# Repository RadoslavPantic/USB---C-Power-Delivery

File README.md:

# 100W USB-C Power Delivery Module

A high-power USB-C Power Delivery (PD) module capable of delivering up to **100W (20V @ 5A)**. 

---

## Project Contents

This repository includes:
- KiCad design files (`.kicad_pro`, `.kicad_pcb`, `.kicad_sch`)
- **Gerber files** for PCB fabrication
- **BOM** file (`usb_c_pd_source.csv`)

---

## Description

The project is based around the STUSB4710 Autonomous USB PD controller IC. The design functions as a power source with short-circuit protection and Vbus monitoring.
The project is configured in a buck topology, meaning there is a constant 24 V DC voltage at the input of the circuit. Using the TPS56837HRPAR buck converter, the PD IC sets the output USB-C compliant voltage. The project is hardware-heavy — the MCU is only needed to monitor the buck converter and to increase the current on the 20 V PDO from 2.25 A to 5 A

## Schematic

The schematic of the circuit is shown below:

---

## 3D View

The 3D render of the assembled PCB:

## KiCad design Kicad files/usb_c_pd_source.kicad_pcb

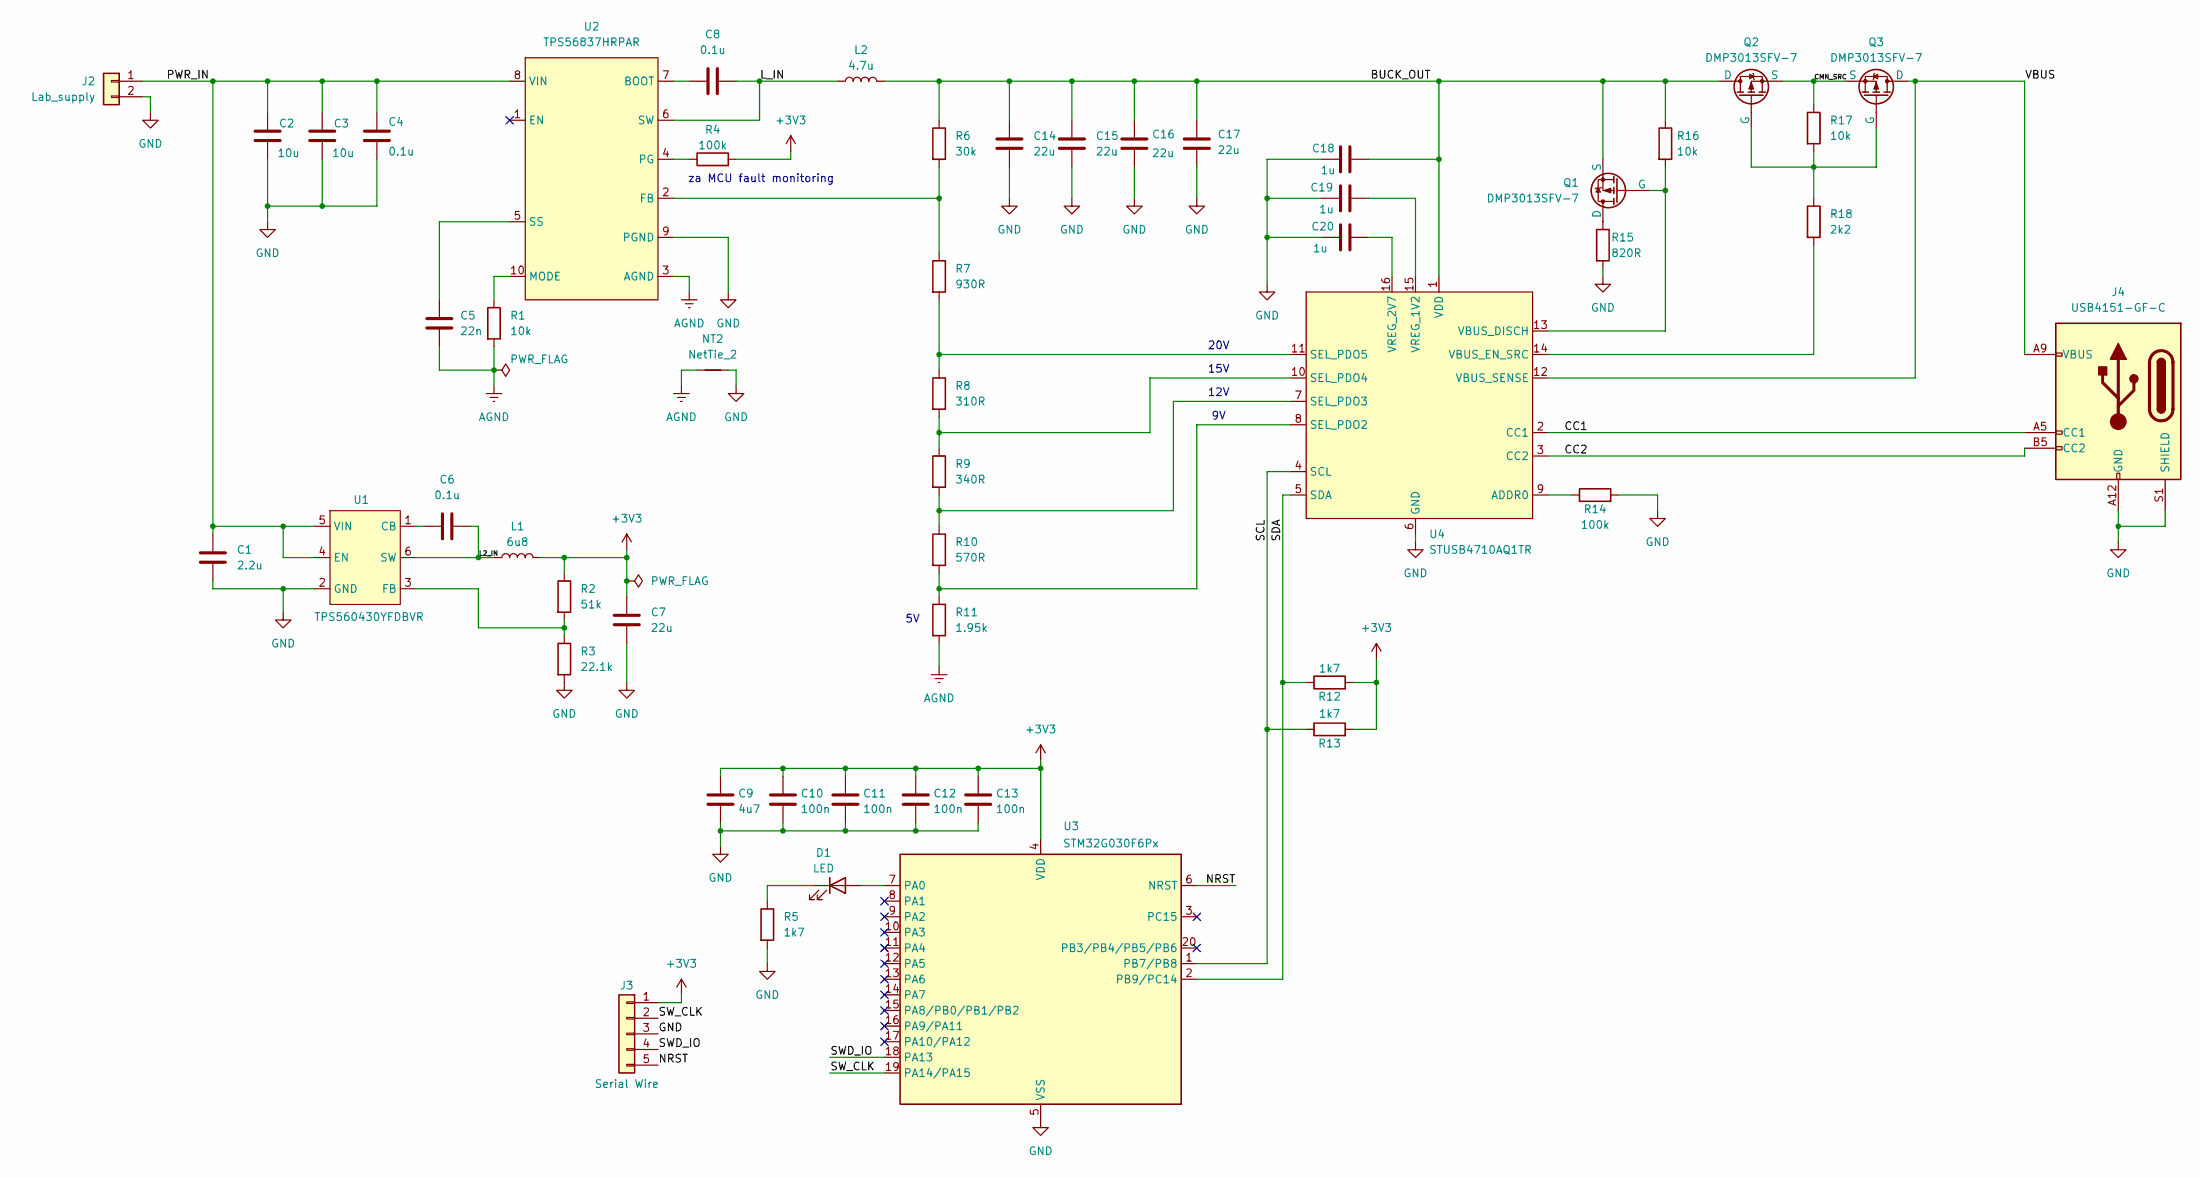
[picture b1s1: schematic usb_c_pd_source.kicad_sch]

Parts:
C1: 2.2u; C_0805_2012Metric_Pad1.18x1.45mm_HandSolder
C2, C3: 10u; C_0805_2012Metric_Pad1.18x1.45mm_HandSolder
C4, C6: 0.1u; C_0805_2012Metric_Pad1.18x1.45mm_HandSolder
C5: 22n; C_0603_1608Metric
C7, C14, C15, C16, C17: 22u; C_0805_2012Metric_Pad1.18x1.45mm_HandSolder
C8: 0.1u; C_0603_1608Metric
C9: 4u7; C_0805_2012Metric_Pad1.18x1.45mm_HandSolder
C10, C11, C12, C13: 100n; C_0805_2012Metric_Pad1.18x1.45mm_HandSolder
C18, C19, C20: 1u; C_0805_2012Metric_Pad1.18x1.45mm_HandSolder
D1: LED; LED_0805_2012Metric
J2: Lab_supply; PhoenixContact_MC_1,5_2-G-3.5_1x02_P3.50mm_Horizontal
J3: Serial Wire; PinHeader_1x05_P2.54mm_Vertical
J4: USB4151-GF-C; USB4151GFC
L1: 6u8; L_1008_2520Metric
L2: 4.7u; L_Taiyo-Yuden_MD-5050
NT2: NetTie_2; NetTie-2_SMD_Pad0.5mm
Q1, Q2, Q3: DMP3013SFV-7; Diodes_PowerDI3333-8
R1: 10k; R_0603_1608Metric
R2: 51k; R_0805_2012Metric_Pad1.20x1.40mm_HandSolder
R3: 22.1k; R_0805_2012Metric_Pad1.20x1.40mm_HandSolder
R4: 100k; R_0603_1608Metric
R5, R12, R13: 1k7; R_0805_2012Metric_Pad1.20x1.40mm_HandSolder
R6: 30k; R_0603_1608Metric
R7: 930R; R_0603_1608Metric
R8: 310R; R_0603_1608Metric
R9: 340R; R_0603_1608Metric
R10: 570R; R_0603_1608Metric
R11: 1.95k; R_0603_1608Metric
R14: 100k; R_0805_2012Metric_Pad1.20x1.40mm_HandSolder
R15: 820R; R_0805_2012Metric_Pad1.20x1.40mm_HandSolder
R16, R17: 10k; R_0805_2012Metric_Pad1.20x1.40mm_HandSolder
R18: 2k2; R_0805_2012Metric_Pad1.20x1.40mm_HandSolder
U1: TPS560430YFDBVR; SOT-23-6
U2: TPS56837HRPAR; TPS56A37RPAR
U3: STM32G030F6Px; TSSOP-20_4.4x6.5mm_P0.65mm
U4: STUSB4710AQ1TR; QFN-16-1EP_3x3mm_P0.5mm_EP1.7x1.7mm

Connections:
+3V3: C7.2, C9.1, C10.1, C11.1, C12.1, C13.1, J3.1, L1.2, R2.1, R4.2, R12.2, R13.2, U3.4 (VDD)
/BUCK_OUT: C14.2, C15.2, C16.2, C17.2, C18.2, L2.2, Q1.1 (S), Q1.2 (S), Q1.3 (S), Q2.5 (D), R6.1, R16.1, U4.1 (VDD)
/CC1: J4.A5 (CC1), U4.2 (CC1)
/CC2: J4.B5 (CC2), U4.3 (CC2)
/CMN_SRC: Q2.1 (S), Q2.2 (S), Q2.3 (S), Q3.1 (S), Q3.2 (S), Q3.3 (S), R17.1
/L2_IN: C6.2, L1.1, U1.6 (SW)
/L_IN: C8.1, L2.1, U2.6 (SW)
/NRST: J3.5, U3.6 (NRST)
/PWR_IN: C1.1, C2.1, C3.1, C4.1, J2.1, U1.4 (EN), U1.5 (VIN), U2.8 (VIN)
/SCL: R13.1, U3.1 (PB7/PB8), U4.4 (SCL)
/SDA: R12.1, U3.2 (PB9/PC14), U4.5 (SDA)
/SWD_IO: J3.4, U3.18 (PA13)
/SW_CLK: J3.2, U3.19 (PA14/PA15)
/VBUS: J4.A4 (VBUS), J4.A9 (VBUS), J4.B4 (VBUS), J4.B9 (VBUS), Q3.5 (D), U4.12 (VBUS_SENSE)
AGND: C5.2, NT2.1, R1.2, R11.2, U2.3 (AGND)
GND: C1.2, C2.2, C3.2, C4.2, C7.1, C9.2, C10.2, C11.2, C12.2, C13.2, C14.1, C15.1, C16.1, C17.1, C18.1, C19.1, C20.1, J2.2, J3.3, J4.A1 (GND), J4.A12 (GND), J4.B1 (GND), J4.B12 (GND), J4.S1 (SHIELD), NT2.2, R3.2, R5.2, R14.2, R15.2, U1.2 (GND), U2.9 (PGND), U3.5 (VSS), U4.6 (GND)
unnamed: D1.2 (A), U3.7 (PA0)
unnamed: D1.1 (K), R5.1
unnamed: Q1.5 (D), R15.1
unnamed: Q1.4 (G), R16.2, U4.13 (VBUS_DISCH)
unnamed: Q2.4 (G), Q3.4 (G), R17.2, R18.1
unnamed: C6.1, U1.1 (CB)
unnamed: R2.2, R3.1, U1.3 (FB)
unnamed: C8.2, U2.7 (BOOT)
unnamed: R6.2, R7.1, U2.2 (FB)
unnamed: R1.1, U2.10 (MODE)
unnamed: R4.1, U2.4 (PG)
unnamed: C5.1, U2.5 (SS)
unnamed: R14.1, U4.9 (ADDR0)
unnamed: R10.2, R11.1, U4.8 (SEL_PDO2)
unnamed: R9.2, R10.1, U4.7 (SEL_PDO3)
unnamed: R8.2, R9.1, U4.10 (SEL_PDO4)
unnamed: R7.2, R8.1, U4.11 (SEL_PDO5)
unnamed: R18.2, U4.14 (VBUS_EN_SRC)
unnamed: C19.2, U4.15 (VREG_1V2)
unnamed: C20.2, U4.16 (VREG_2V7)

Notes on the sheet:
15V
12V
za MCU fault monitoring
20V

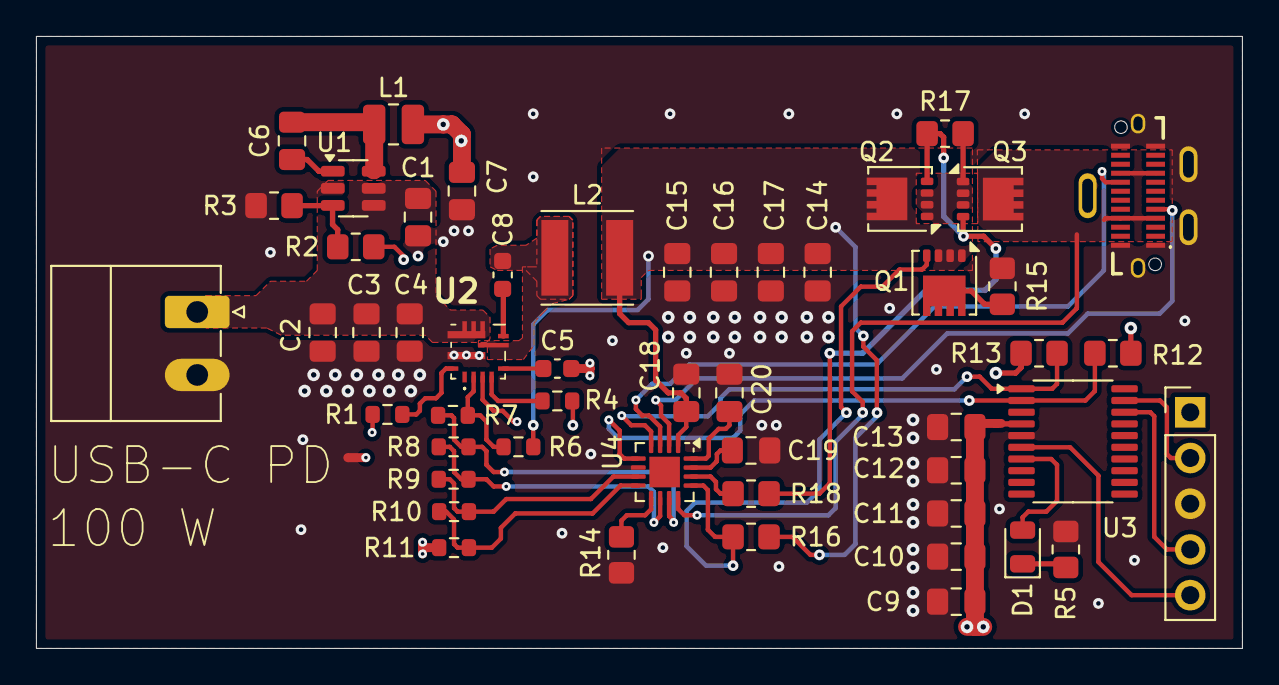
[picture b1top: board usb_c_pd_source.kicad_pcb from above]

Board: 4 copper layers, 67.0 x 34.0 mm, 52 parts (0 on the bottom side), 36 nets.

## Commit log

2025-07-28 Initial commit: USB-C PD PCB project files
